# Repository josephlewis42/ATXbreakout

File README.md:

ATX Breakout Board
==================

An ATX power supply breakout. Eagle files are included.

Features
--------

* Small footprint 1.5" x 3" (38 x 76mm) greatly beats Dangerous Prototype's
* Large traces so you can pull power without burning traces (unlike SpartFun's)
* Large, sturdy mounting-holes with edge clearance means no more torn boards
* Optional power indicator LED
* Optional resettable fuses (can be bypassed with a jumper)
* Supports posts and break-away headers for powering your projects--good for both benchtop and embedded use
* On/Off switch
* Supports both 20 and 24 pin ATX

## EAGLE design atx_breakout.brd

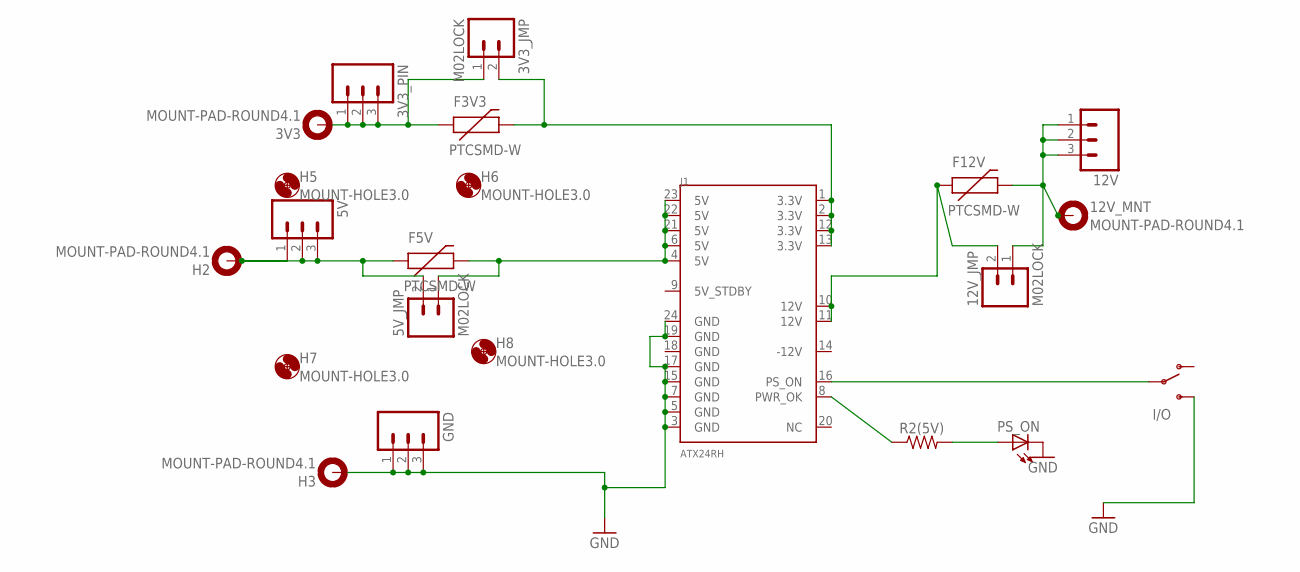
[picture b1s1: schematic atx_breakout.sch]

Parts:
3V3, 12V_MNT: MOUNT-PAD-ROUND4.1; 4,1-PAD
3V3_JMP, 5V_JMP, 12V_JMP: M02LOCK; 1X02_LOCK
3V3_PIN, 5V, 12V: M031X03_NO_SILK; 1X03_NO_SILK
F3V3, F5V, F12V: PTCSMD-W; PTC-1206-WIDE
GND: M031X03_NO_SILK; 1X03_NO_SILK
H2, H3: MOUNT-PAD-ROUND4.1; 4,1-PAD
H5, H6, H7, H8: MOUNT-HOLE3.0; 3,0
I/O: SWITCH-SPDTPTH; SWITCH-SPDT
J1: ATX24RH; ATX24_RIGHT_ANGLE
PS_ON: LED-3MM-NO_SILK; LED3MM-NS
R2(5V): RESISTORAXIAL-0.3; AXIAL-0.3

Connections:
5VFUSE: 5V.1, 5V.2, 5V.3, 5V_JMP.2, F5V.1, H2.B4,1
GND: GND.1, GND.2, GND.3, H3.B4,1, I/O.3 (S), J1.3 (GND), J1.5 (GND), J1.7 (GND), J1.15 (GND), J1.17 (GND), J1.19 (GND), J1.24 (GND), PS_ON.K (C)
unnamed: J1.8 (PWR_OK), R2(5V).P$1 (1)
unnamed: 3V3_JMP.2, F3V3.2, J1.1 (3.3V), J1.2 (3.3V), J1.12 (3.3V), J1.13 (3.3V)
unnamed: 12V_JMP.2, F12V.1, J1.10 (12V), J1.11 (12V)
unnamed: 3V3.B4,1, 3V3_JMP.1, 3V3_PIN.1, 3V3_PIN.2, 3V3_PIN.3, F3V3.1
unnamed: 5V_JMP.1, F5V.2, J1.4 (5V), J1.6 (5V), J1.21 (5V), J1.22 (5V), J1.23 (5V)
unnamed: 12V.1, 12V.2, 12V.3, 12V_JMP.1, 12V_MNT.B4,1, F12V.2
unnamed: PS_ON.A, R2(5V).P$2 (2)
unnamed: I/O.2, J1.16 (PS_ON)

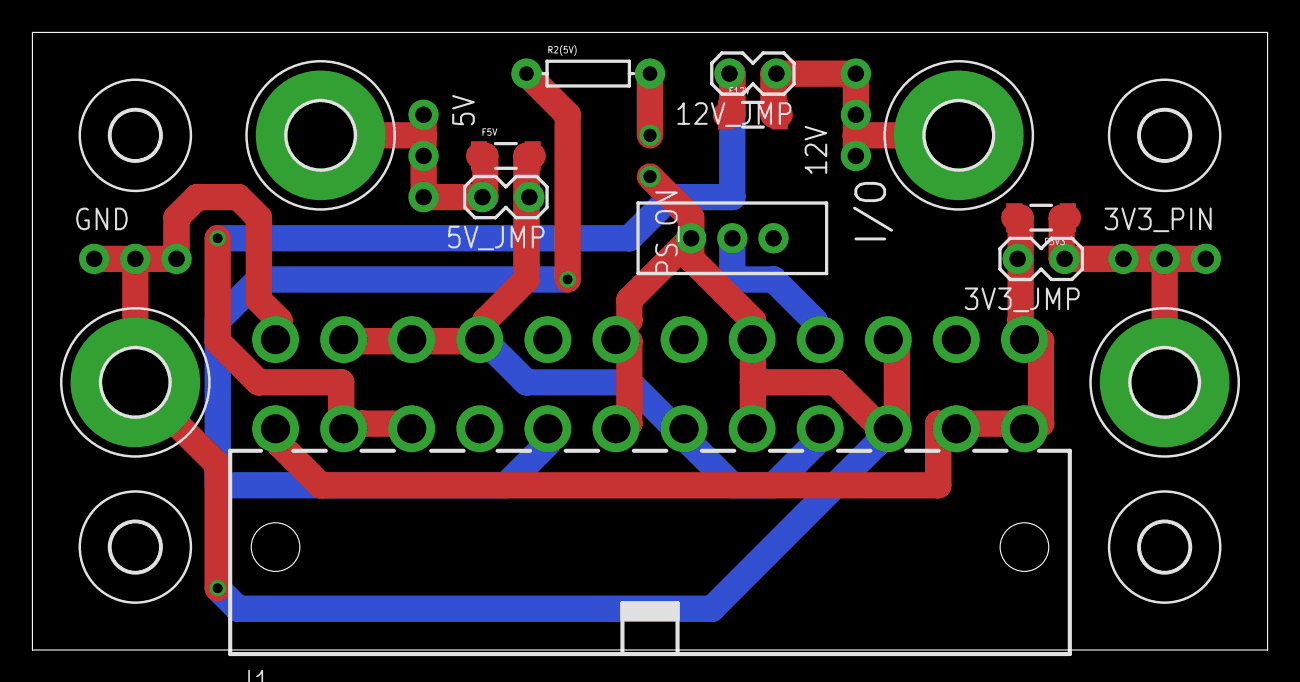
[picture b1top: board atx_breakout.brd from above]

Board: 2 copper layers, 76.2 x 38.1 mm, 22 parts (0 on the bottom side), 10 nets.

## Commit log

2015-12-19 Added board image

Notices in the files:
parts and their libraries:
SparkFun-Connectors: Licensing: CC v3.0 Share-Alike You are welcome to use this library for commercial purposes.
